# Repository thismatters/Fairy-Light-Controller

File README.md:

# Fairy Light Controller

Initially when we bought [fairy lights](https://www.amazon.com/gp/product/B00I7M7C40/) (sorry for the amazon link, I hope it stays valid for a while) they came with crappy wall warts which had to be plugged and unplugged daily; these wall warts were of such poor quality that the barrel plug which recieved the light strand would inevitably break. 
Totally unacceptable.
The goal of this project is to provide an easy interface for controlling and powering many strands of LED fairy lights.

## Features

* 40 Watt Power supply,
* ATMega328P,
* IR Reciever and [Remote Control](https://www.sparkfun.com/products/11759) [also works with a little white apple remote if you have one laying around],
* Barrel Plugs for 8 light strands,
* Laser cut acrylic case.

## What's included

* Code for the ATMega328P,
* KiCAD files for the control board ([OSHPark project for this board](https://oshpark.com/shared_projects/VDE5yBSG)),
* Bill of Materials (below),
* SVG files for cutting the case parts.

## Bill of Materials

Here is what you'll need to order to build this thing. I generally order the parts from a few different suppliers due to availability and price so bear with me. You'll also need a board (obvs), you can order some from OSHPark by following the link above, or you can etch your own. Your choice! 

| Part # | Qty | Reference | Description | MFR # (link) | Supplier | Notes |
|--------|-----|-----------|-------------|--------------|----------|-------|
|1|1|C1|Capacitor 100uF (SMD-1206)|[GRM31CD80J107ME39L](https://www.mouser.com/ProductDetail/81-GRM31CD80J107ME9L)|Mouser||
|2|1|C2|Capacitor 10uF (SMD-0805)|[GRM21BC81C106ME15L](https://www.mouser.com/ProductDetail/Murata-Electronics/GRM21BC81C106ME15L?qs=sGAEpiMZZMs0AnBnWHyRQKFZIQ7b73cd5p1OjeXSJs7IZ5GPsfC2iQ%3d%3d)|Mouser||
|3|1|C3|Capacitor 100nF (SMD-0805)|[100nF 50V 0805](https://www.taydaelectronics.com/100nf-50v-smd-ceramic-chip-capacitor.html)|Tayda|If you order 100 of these they will last you a long time.|
|4|1|C4|Capacitor 1uF (Radial D5L11)|[105CKR100M](https://www.mouser.com/ProductDetail/Illinois-Capacitor-CDE/105CKR100M?qs=sGAEpiMZZMtZ1n0r9vR22fPWwtj8kO8aXBFG7%252b0kMMHBNQpcXdefQA%3d%3d)|Mouser||
|5|8|CON1--CON8|Barrel Jack|[KLDX-SMT-0202-AP](https://www.mouser.com/ProductDetail/806-KLDX-SMT0202AP)|Mouser|These are sized to fit the fairy lights linked below.|
|6|1|IC1|Microcontroller|[ATMEGA328P-P](https://www.taydaelectronics.com/atmega328p-pu-atmega328-microcontroller-ic.html)|Tayda|An Arduino chip without the Arduino board. You'll have to have a means to program it (an Arduino board will work nicely for that)|
|7|1|P1|Connector 4POS|[B4PS-VH(LF) (SN)](https://www.digikey.com/product-detail/en/jst-sales-america-inc/B4PS-VH(LF)(SN)/455-1650-ND/926557)|Digi-key|Receive the power onto the board.|
|8|8|Q1--Q8|NPN Darlinton Pair (SOT-223)|[FZT600TA](https://www.mouser.com/ProductDetail/522-FZT600TA)|Mouser||
|9|8|R1--R8|Resistor 0.27 Ohm (Thru-hole)|[MOSX1CT52RR27J](https://www.mouser.com/ProductDetail/660-MOSX1CT52RR27J)|Mouser||
|10|1|R9|Resistor 0 Ohm (SMD-0805)|[0 Ohm 1/8W 1% 0805](https://www.taydaelectronics.com/50-x-smd-chip-resistors-0-ohm-1-8w-1-0805.html)|Tayda|If you order 100 of these they will last you a long time.|
|11|1|R10|Resistor 100 Ohm (SMD-0805)|[100 Ohm 1/8W 1% 0805](https://www.taydaelectronics.com/50-x-smd-chip-resistors-100-ohm-1-8w-1-0805.html)|Tayda|If you order 100 of these they will last you a long time.|
|12|1|R11|Resistor 10k Ohm (SMD-0805)|[10K Ohm 1/8W 1% 0805](https://www.taydaelectronics.com/50-x-smd-chip-resistors-10k-ohm-1-8w-1-0805.html)|Tayda|If you order 100 of these they will last you a long time.|
|13|2|RR1--RR2|Resistor Array (Bussed) 10k Ohm (SIP-9)|[4609X-101-103LF](https://www.mouser.com/ProductDetail/652-4609X-1LF-10K)|Mouser|8 Resistors| 9 Pins|
|14|1|U1|IR Reciever (38 khz)|[TSOP34438](https://www.mouser.com/ProductDetail/522-FZT600TA)|Mouser||
|15|1|X1|Crystal Oscillator (with Caps)|[CSTLS8M00G53-A0](https://www.mouser.com/ProductDetail/81-CSTLS8M00G53-A0)|Mouser||
|16|1|NA|Power Supply 40W|[EPS-45-5-C](https://www.mouser.com/ProductDetail/709-EPS45-5-C)|Mouser||
|17|10|NA|Connector Terminal Crimp-ons|[SVH-41T-P1.1](https://www.digikey.com/product-detail/en/jst-sales-america-inc/SVH-41T-P1.1/455-1319-1-ND/608888)|Digi-key|Those little silver things you have to smash onto your wires.|
|18|2|NA|Connector Housing 4POS|[VHR-4N](https://www.digikey.com/product-detail/en/jst-sales-america-inc/VHR-4N/455-1185-ND/608626)|Digi-key|To get power from the power supply to the board|
|19|1|NA|Connector Housing 3POS|[VHR-3N](https://www.digikey.com/product-detail/en/jst-sales-america-inc/VHR-3N/455-1184-ND/608625)|Digi-key|To get power from the wall to the power supply|
|20|1|NA|Remote Control|[COM-11759](https://www.sparkfun.com/products/11759)|Sparkfun|The software also supports the little white Apple remote control| but the sparkfun one allows more features.|
|21|1|NA|Power Cord||stayonline.com|The power supply insists on being grounded, and I am happy to oblige it. You can use an old PC power cable with one end cut off (choose wisely), or you can order to length.|
|22|8|NA|Fairy Lights|[B00I7M7C40](https://www.amazon.com/gp/product/B00I7M7C40/)|Amazon|It is pretty vital to get the ones with the barrel power connector that matches the barrel jacks (Item 5). Minimum 1, maximum 8|
|23|1|NA|Battery for Remote Control|CR2025|Lots of places|You figure it out|
|24|1|NA|28 pin DIP IC Socket|[28 pin DIP IC Socket](https://www.taydaelectronics.com/28-pin-dip-ic-socket-adaptor-solder-type.html)|Tayda|This is what you'll actually solder to the board. Cram the ATMega328 into this.

## The Case

The case is cut from 0.177 inch thick acyrlic sheet using a laser cutter. The [specific laser cutter](http://atxhs.org/wiki/Hosted/10000045) I used is at the ATX Hackerspace; it does not compensate for kerf so the files themselves compensate for the laser width. The case parts should fit together snugly so no adhesive is needed for assembly, although the little bits for wall mounting will need to be bonded onto the bottom so a little cyanoacrylate adhesive will be useful.

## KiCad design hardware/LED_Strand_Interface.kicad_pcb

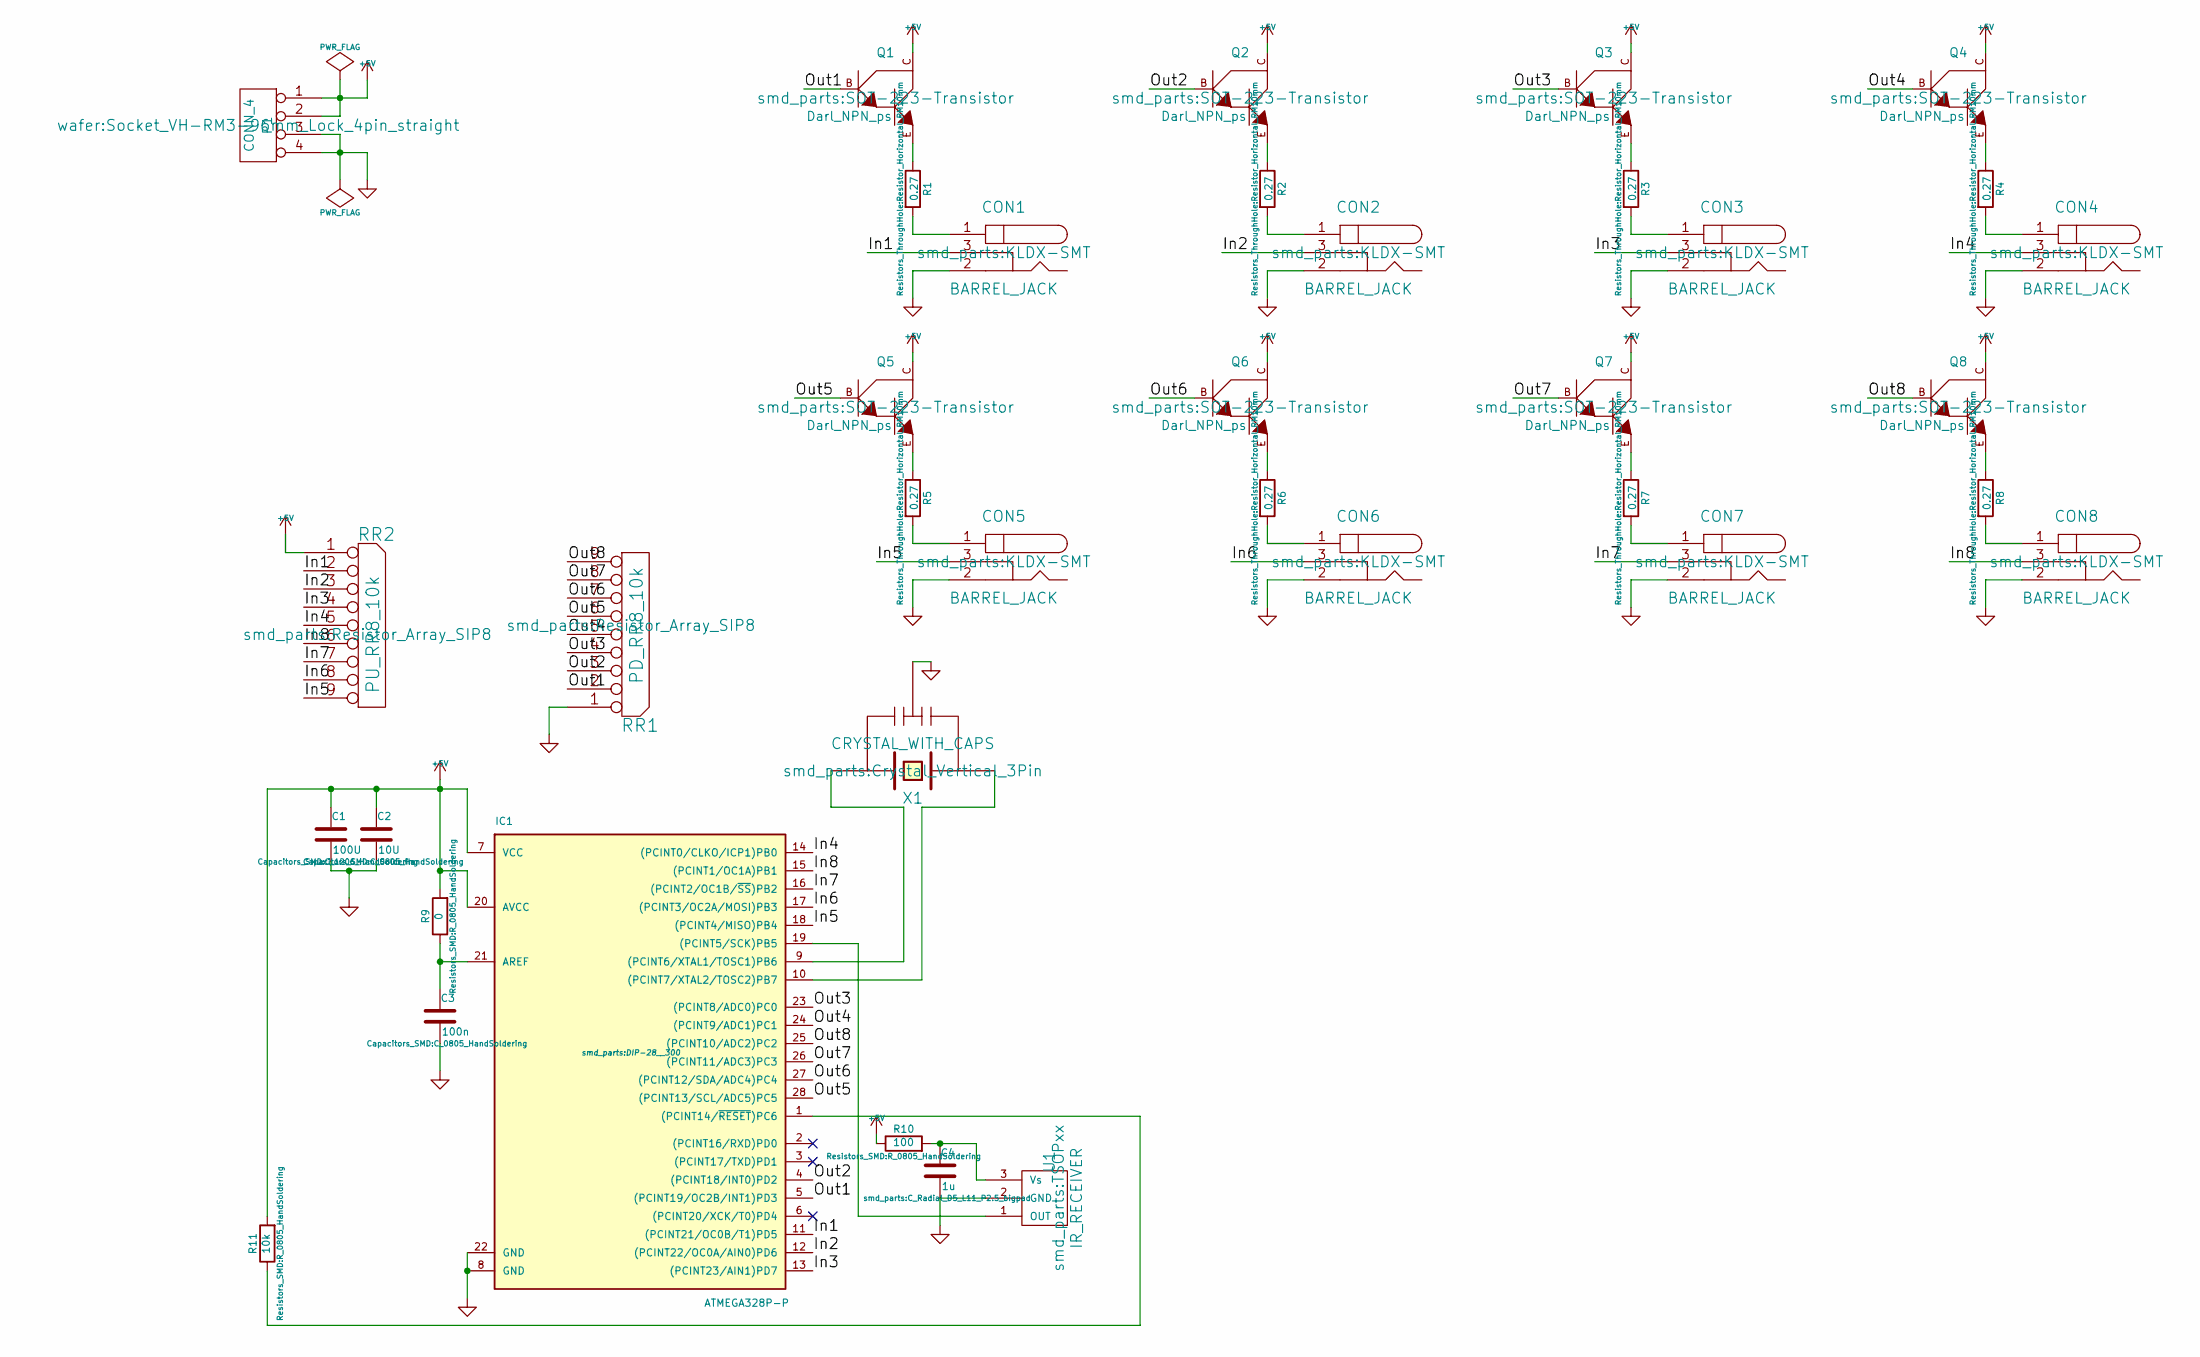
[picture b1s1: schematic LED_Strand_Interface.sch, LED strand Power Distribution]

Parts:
C1: 100U; C_1206_HandSoldering
C2: 10U; C_0805_HandSoldering
C3: 100n; C_0805_HandSoldering
C4: 1u; C_Radial_D5_L11_P2.5_bigpad
CON1, CON2, CON3, CON4, CON5, CON6, CON7, CON8: BARREL_JACK; KLDX-SMT
IC1: ATMEGA328P-P; DIP-28__300
P1: CONN_4; Socket_VH-RM3-96mm_Lock_4pin_straight
Q1, Q2, Q3, Q4, Q5, Q6, Q7, Q8: Darl_NPN_ps; SOT-223-Transistor
R1, R2, R3, R4, R5, R6, R7, R8: 0.27; Resistor_Horizontal_RM10mm
R9: 0; R_0805_HandSoldering
R10: 100; R_0805_HandSoldering
R11: 10k; R_0805_HandSoldering
RR1: PD_RR8_10k; Resistor_Array_SIP8
RR2: PU_RR8_10k; Resistor_Array_SIP8
U1: IR_RECEIVER; TSOPxx
X1: CRYSTAL_WITH_CAPS; Crystal_Vertical_3Pin

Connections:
+5V: C1.1, C2.1, IC1.7 (VCC), IC1.20 (AVCC), P1.1, P1.2, Q1.C, Q2.C, Q3.C, Q4.C, Q5.C, Q6.C, Q7.C, Q8.C, R9.2, R10.1, R11.2, RR2.1 (COM)
/In1: CON1.3, IC1.11 ((PCINT21/OC0B/T1)PD5), RR2.2
/In2: CON2.3, IC1.12 ((PCINT22/OC0A/AIN0)PD6), RR2.3
/In3: CON3.3, IC1.13 ((PCINT23/AIN1)PD7), RR2.4
/In4: CON4.3, IC1.14 ((PCINT0/CLKO/ICP1)PB0), RR2.5
/In5: CON5.3, IC1.18 ((PCINT4/MISO)PB4), RR2.9
/In6: CON6.3, IC1.17 ((PCINT3/OC2A/MOSI)PB3), RR2.8
/In7: CON7.3, IC1.16 ((PCINT2/OC1B/~SS~)PB2), RR2.7
/In8: CON8.3, IC1.15 ((PCINT1/OC1A)PB1), RR2.6
/Out1: IC1.5 ((PCINT19/OC2B/INT1)PD3), Q1.B, RR1.2
/Out2: IC1.4 ((PCINT18/INT0)PD2), Q2.B, RR1.3
/Out3: IC1.23 ((PCINT8/ADC0)PC0), Q3.B, RR1.4
/Out4: IC1.24 ((PCINT9/ADC1)PC1), Q4.B, RR1.5
/Out5: IC1.28 ((PCINT13/SCL/ADC5)PC5), Q5.B, RR1.6
/Out6: IC1.27 ((PCINT12/SDA/ADC4)PC4), Q6.B, RR1.7
/Out7: IC1.26 ((PCINT11/ADC3)PC3), Q7.B, RR1.8
/Out8: IC1.25 ((PCINT10/ADC2)PC2), Q8.B, RR1.9
GND: C1.2, C2.2, C3.2, C4.2, CON1.2, CON2.2, CON3.2, CON4.2, CON5.2, CON6.2, CON7.2, CON8.2, IC1.8 (GND), IC1.22 (GND), P1.3, P1.4, RR1.1 (COM), U1.2 (GND), X1.2 (GND)
unnamed: C3.1, IC1.21 (AREF), R9.1
unnamed: C4.1, R10.2, U1.3 (Vs)
unnamed: CON1.1, R1.2
unnamed: CON2.1, R2.2
unnamed: CON3.1, R3.2
unnamed: CON4.1, R4.2
unnamed: CON5.1, R5.2
unnamed: CON6.1, R6.2
unnamed: CON7.1, R7.2
unnamed: CON8.1, R8.2
unnamed: IC1.1 ((PCINT14/~RESET~)PC6), R11.1
unnamed: IC1.9 ((PCINT6/XTAL1/TOSC1)PB6), X1.3
unnamed: IC1.10 ((PCINT7/XTAL2/TOSC2)PB7), X1.1
unnamed: IC1.19 ((PCINT5/SCK)PB5), U1.1 (OUT)
unnamed: Q1.E, R1.1
unnamed: Q2.E, R2.1
unnamed: Q3.E, R3.1
unnamed: Q4.E, R4.1
unnamed: Q5.E, R5.1
unnamed: Q6.E, R6.1
unnamed: Q7.E, R7.1
unnamed: Q8.E, R8.1

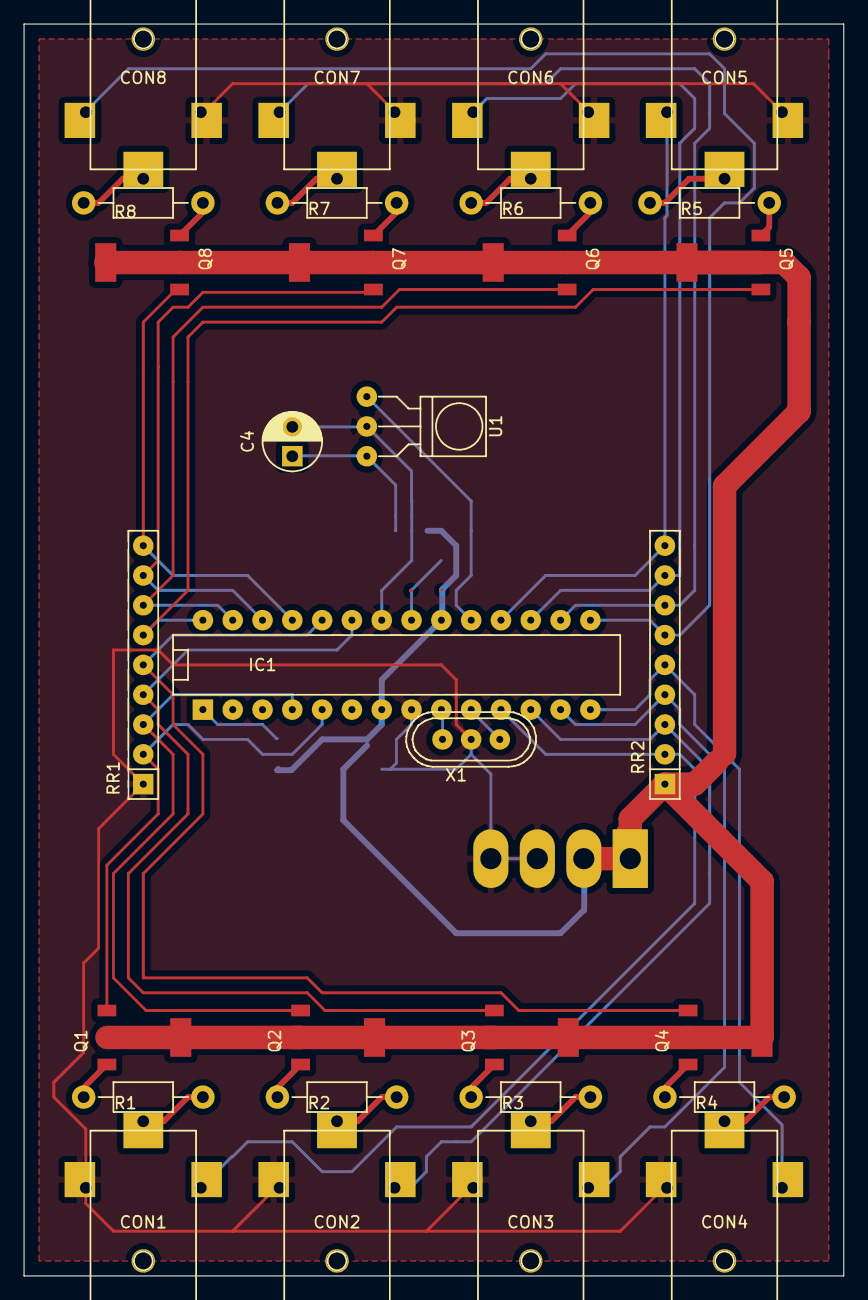
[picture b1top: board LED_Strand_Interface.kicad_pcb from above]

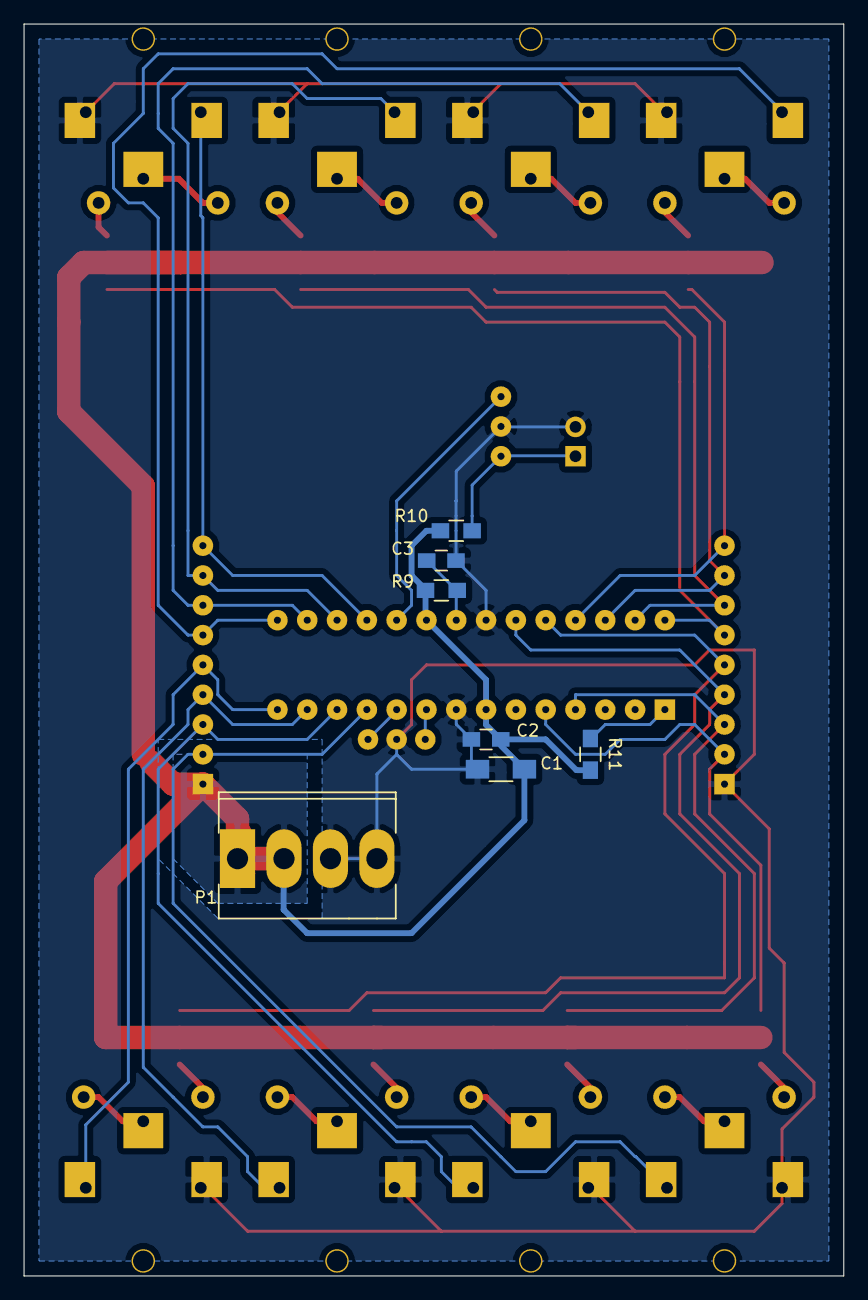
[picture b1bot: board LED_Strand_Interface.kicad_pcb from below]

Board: 2 copper layers, 69.8 x 106.7 mm, 37 parts (7 on the bottom side), 40 nets.

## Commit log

2018-04-14 added link
2018-04-14 updated BOM added photo describing remote control functions
2018-04-14 quick changes to the readme
2018-04-14 more fixes to readme
2018-04-14 added readme section for the case
